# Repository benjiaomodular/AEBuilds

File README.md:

# AEBuilds
[![CC BY 4.0][cc-by-shield]][cc-by]

A collection of DIY projects I made for my AE modular synthesizer system.

## Modules

| Name        | Description | Category     |
| :---        | :----       |          ---: |
| [001-Clock](/001-Clock/)       | A clock based on [robstave's ACS-85-0020 "Adjustable Square Wave"](https://github.com/robstave/ArduinoComponentSketches/tree/master/ACS-85%20ATTiny85%20sketches/ACS-85-0020). Adjustable rate and duty cycle %.       | Clocks, ATtiny85   |
|  [002-Random](/002-Random)   | Generates randomized gates based on a probability knob. Module based on [robstave's ACS-85-0613 "Coin Flip"](https://github.com/robstave/ArduinoComponentSketches/tree/master/ACS-85%20ATTiny85%20sketches/ACS-85-0613).        | Random, ATtiny85      |
|  [003-Quantizer](/003-Quantizer)   | Fixed-scale Arduino quantizer with trigger input| Utility, Arduino Nano      |
|  [004-AdditiveVCO](/004-AdditiveVCO)  | An Arduino VCO based on [HAGIWO's Additive VCO project](https://note.com/solder_state/n/n30b3a8737b1e). | VCO, Arduino Nano |

## LICENSE
All work under this collection is licensed under a
[Creative Commons Attribution 4.0 International License][cc-by], unless noted otherwise.

[cc-by]: http://creativecommons.org/licenses/by/4.0/
[cc-by-shield]: https://img.shields.io/badge/License-CC%20BY%204.0-lightgrey.svg

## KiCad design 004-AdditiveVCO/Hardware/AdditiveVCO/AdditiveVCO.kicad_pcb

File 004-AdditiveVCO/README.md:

# AdditiveVCO
An Arduino VCO based on [HAGIWO's Additive VCO project](https://note.com/solder_state/n/n30b3a8737b1e).

## Circuit

## LICENSE
All work under this collection is licensed under a
[Creative Commons Attribution 4.0 International License][cc-by], unless noted otherwise.

[cc-by]: http://creativecommons.org/licenses/by/4.0/
[cc-by-shield]: https://img.shields.io/badge/License-CC%20BY%204.0-lightgrey.svg

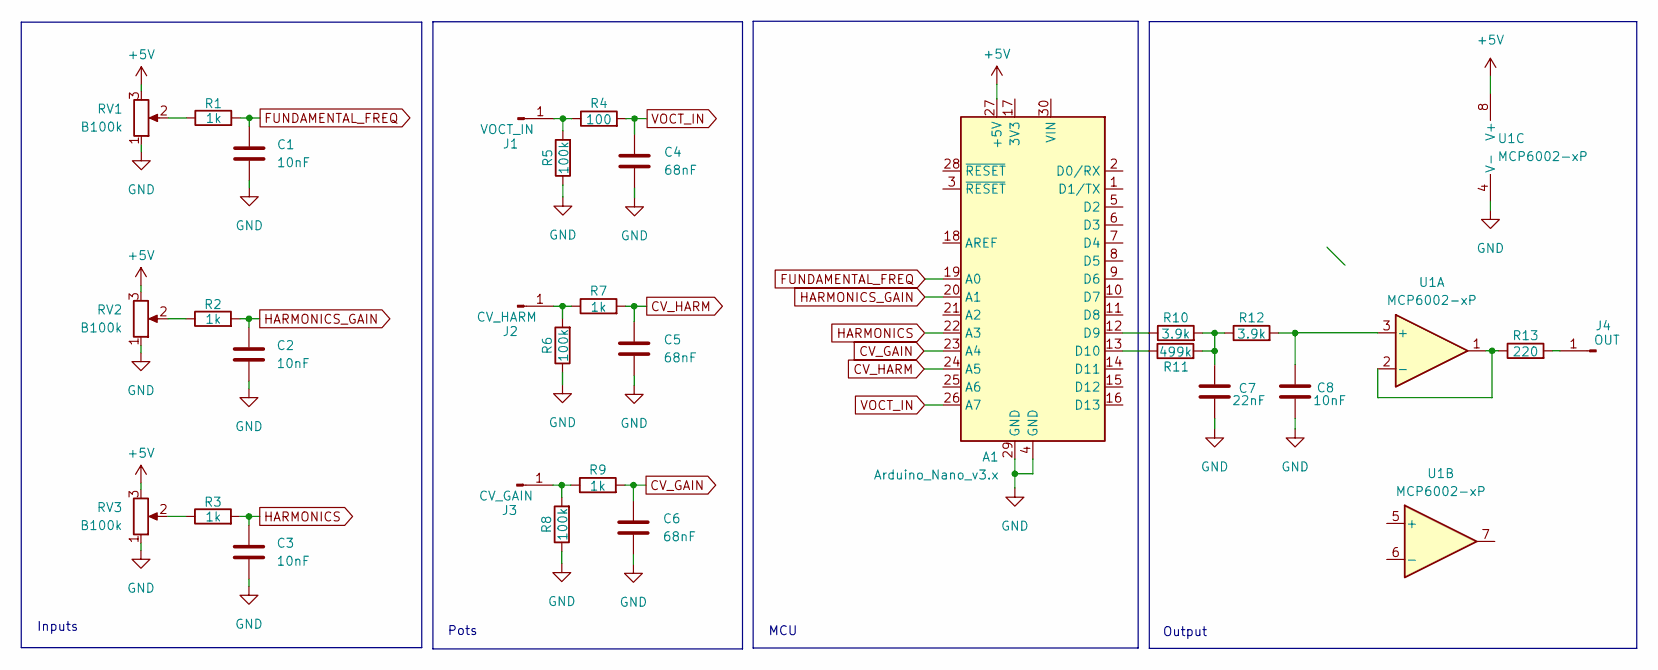
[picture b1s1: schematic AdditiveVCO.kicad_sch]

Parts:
A1: Arduino_Nano_v3.x; Arduino_Nano
C1, C2, C3, C8: 10nF; C_Rect_L7.0mm_W2.0mm_P5.00mm
C4, C5, C6: 68nF; C_Rect_L7.0mm_W2.0mm_P5.00mm
C7: 22nF; C_Rect_L7.0mm_W2.0mm_P5.00mm
J1: VOCT_IN; Pin_D0.7mm_L6.5mm_W1.8mm_FlatFork
J2: CV_HARM; Pin_D0.7mm_L6.5mm_W1.8mm_FlatFork
J3: CV_GAIN; Pin_D0.7mm_L6.5mm_W1.8mm_FlatFork
J4: OUT; Pin_D0.7mm_L6.5mm_W1.8mm_FlatFork
R1, R2, R3, R7, R9: 1k; R_Axial_DIN0207_L6.3mm_D2.5mm_P10.16mm_Horizontal
R4: 100; R_Axial_DIN0207_L6.3mm_D2.5mm_P10.16mm_Horizontal
R5, R6, R8: 100k; R_Axial_DIN0207_L6.3mm_D2.5mm_P10.16mm_Horizontal
R10, R12: 3.9k; R_Axial_DIN0207_L6.3mm_D2.5mm_P10.16mm_Horizontal
R11: 499k; R_Axial_DIN0207_L6.3mm_D2.5mm_P10.16mm_Horizontal
R13: 220; R_Axial_DIN0207_L6.3mm_D2.5mm_P10.16mm_Horizontal
RV1, RV2, RV3: B100k; Potentiometer_Alpha_RD901F-40-00D_Single_Vertical
U1: MCP6002-xP; DIP-8_W7.62mm

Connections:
+5V: A1.27 (+5V), RV1.3, RV2.3, RV3.3, U1.8 (V+)
CV_GAIN: A1.23 (A4), C6.1, R9.2
CV_HARM: A1.24 (A5), C5.1, R7.2
FUNDAMENTAL_FREQ: A1.19 (A0), C1.1, R1.2
GND: A1.4 (GND), A1.29 (GND), C1.2, C2.2, C3.2, C4.2, C5.2, C6.2, C7.2, C8.2, R5.1, R6.1, R8.1, RV1.1, RV2.1, RV3.1, U1.4 (V-)
HARMONICS: A1.22 (A3), C3.1, R3.2
HARMONICS_GAIN: A1.20 (A1), C2.1, R2.2
unnamed: A1.12 (D9), R10.1
unnamed: A1.13 (D10), R11.1
unnamed: C7.1, R10.2, R11.2, R12.1
unnamed: J1.1, R4.1, R5.2
unnamed: J2.1, R6.2, R7.1
unnamed: J3.1, R8.2, R9.1
unnamed: J4.1, R13.2
unnamed: R1.1, RV1.2
unnamed: R2.1, RV2.2
unnamed: R3.1, RV3.2
unnamed: C8.1, R12.2, U1.3 (+)
unnamed: R13.1, U1.1, U1.2 (-)
VOCT_IN: A1.26 (A7), C4.1, R4.2

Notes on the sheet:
Output
Inputs
MCU
Pots

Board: 2 copper layers, 30 parts (9 on the bottom side), 20 nets, no tracks yet.

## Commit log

2024-01-26 Hello git
2024-01-26 Added working code for Random
2024-01-26 Added pinouts on code comments
2024-01-26 Added some docs for Random
2024-01-26 renamed aeclock to clock
2024-01-27 Added schematics for Random
2024-02-11 Added quantizer build
2024-02-11 Added quantizer in catalog
2024-02-15 Started Additive VCO build
2024-02-16 Finished up AdditiveVCO project
2024-02-16 Added license
2024-02-18 Added FMVCO
